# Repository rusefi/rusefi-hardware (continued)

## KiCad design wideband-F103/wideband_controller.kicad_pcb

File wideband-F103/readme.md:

🔴 RED ALERT 🔴 STATUS UNKNOWN 🔴 Most usages are either F042 or lambda-x2, this wideband-F103 design is a bit abandoned we never got perfect HW+FW match 🔴

Self-contained LSU wideband supporting both STM32F103 and GD32F103

See https://github.com/mck1117/wideband

115200 baud

[.ini](https://github.com/dron0gus/wideband/blob/master/firmware/ini/rusefi_wb_f1.ini)

# Changelog

# rev 4

* Iteration of rev 3 with fixed PCB dimensions
* Improved RC filter on digital input lines
* Pinout changes https://github.com/rusefi/rusefi-hardware/pull/153

# rev 3

* New board
* Microcontroller replaced
* Added four digital inputs
* Added bluetooth module
* Now LQFP-64
* In-action demo https://youtu.be/ZzZXdSdfkbs

# rev 2

* Firmware binaries https://github.com/rusefi/rusefi-hardware/releases/tag/20220904
* Silkscreen improvements on back side
* 2x7 debug port moved to top side
* VBatt sense added
* Still LQFP-48

# rev 1

* Works with LQFP-48 STM32 and GD32
* PWM required HW hacks

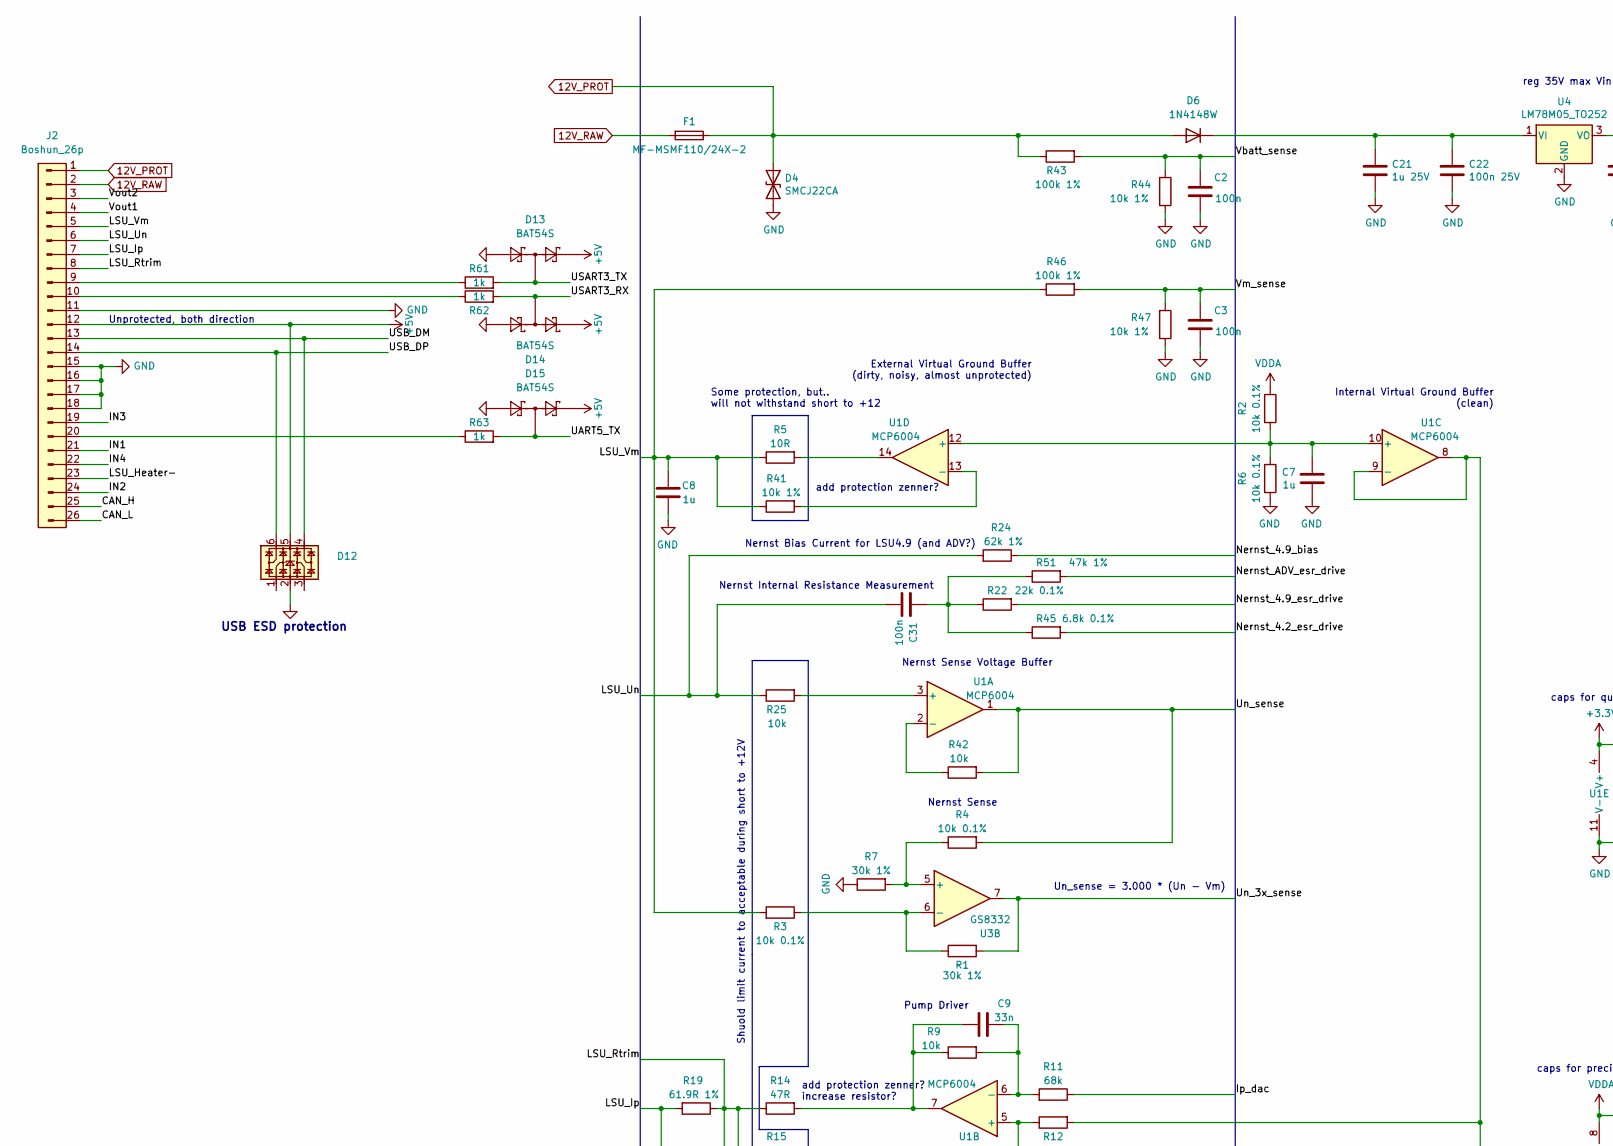
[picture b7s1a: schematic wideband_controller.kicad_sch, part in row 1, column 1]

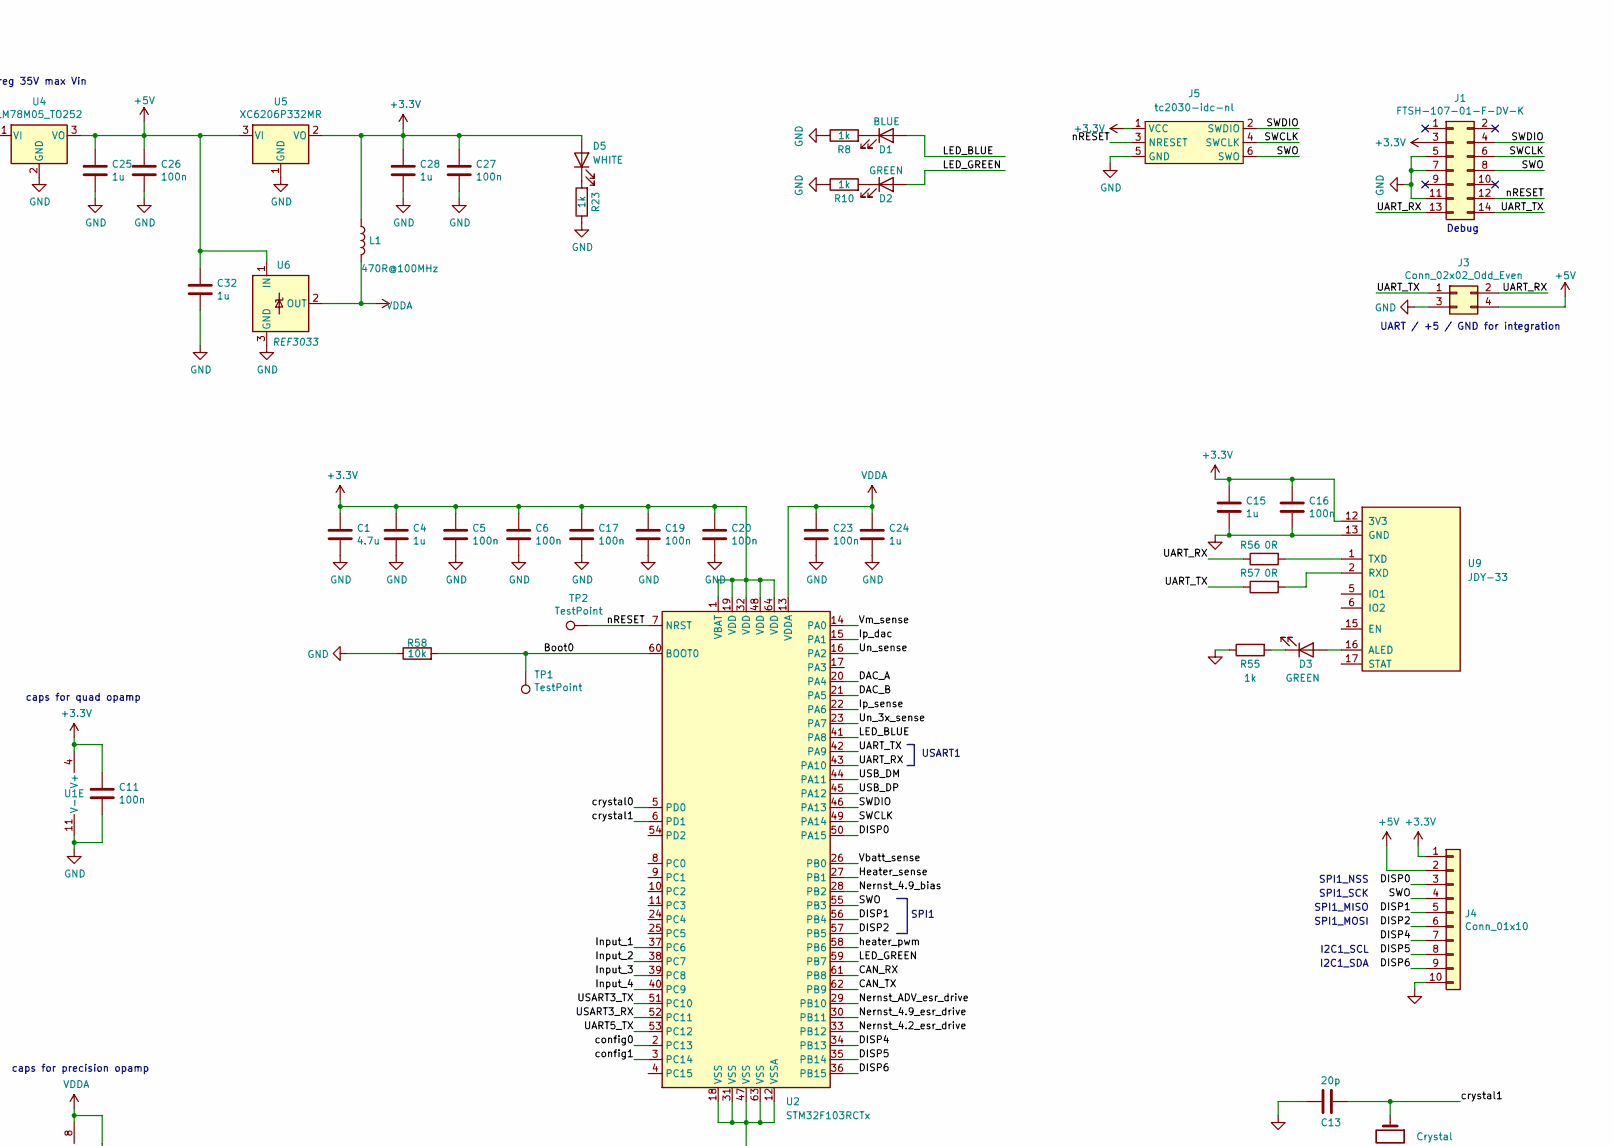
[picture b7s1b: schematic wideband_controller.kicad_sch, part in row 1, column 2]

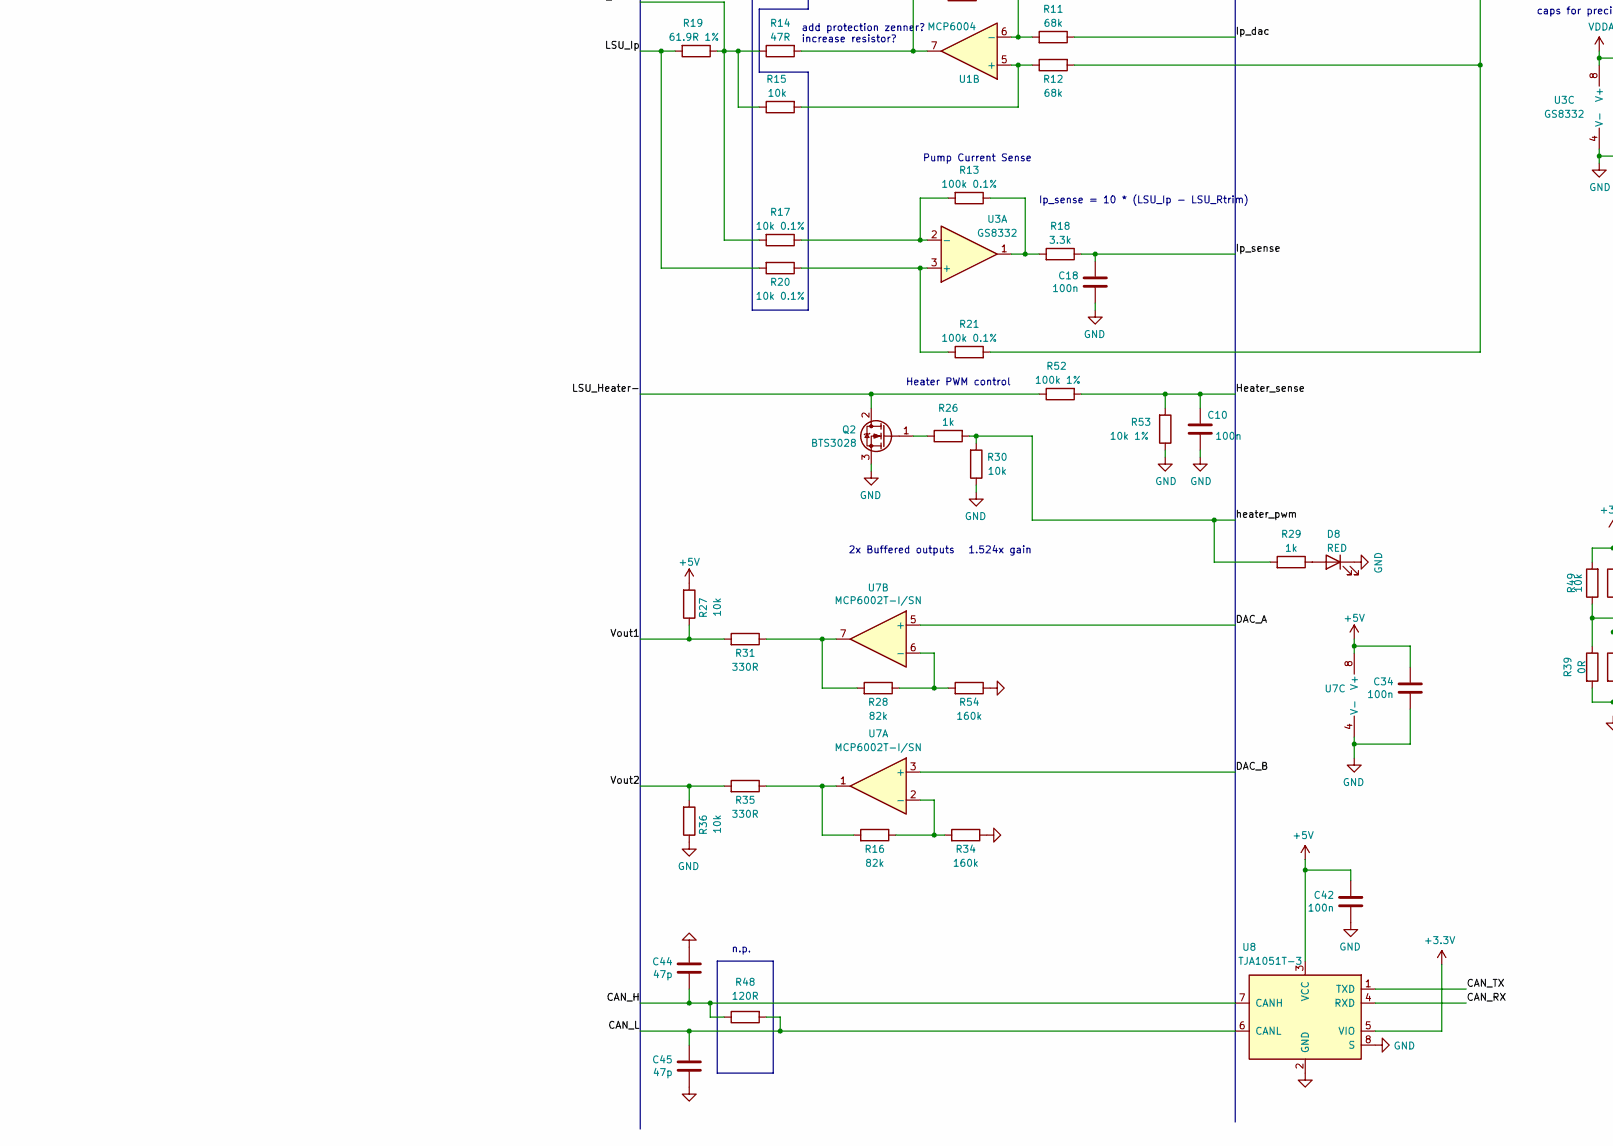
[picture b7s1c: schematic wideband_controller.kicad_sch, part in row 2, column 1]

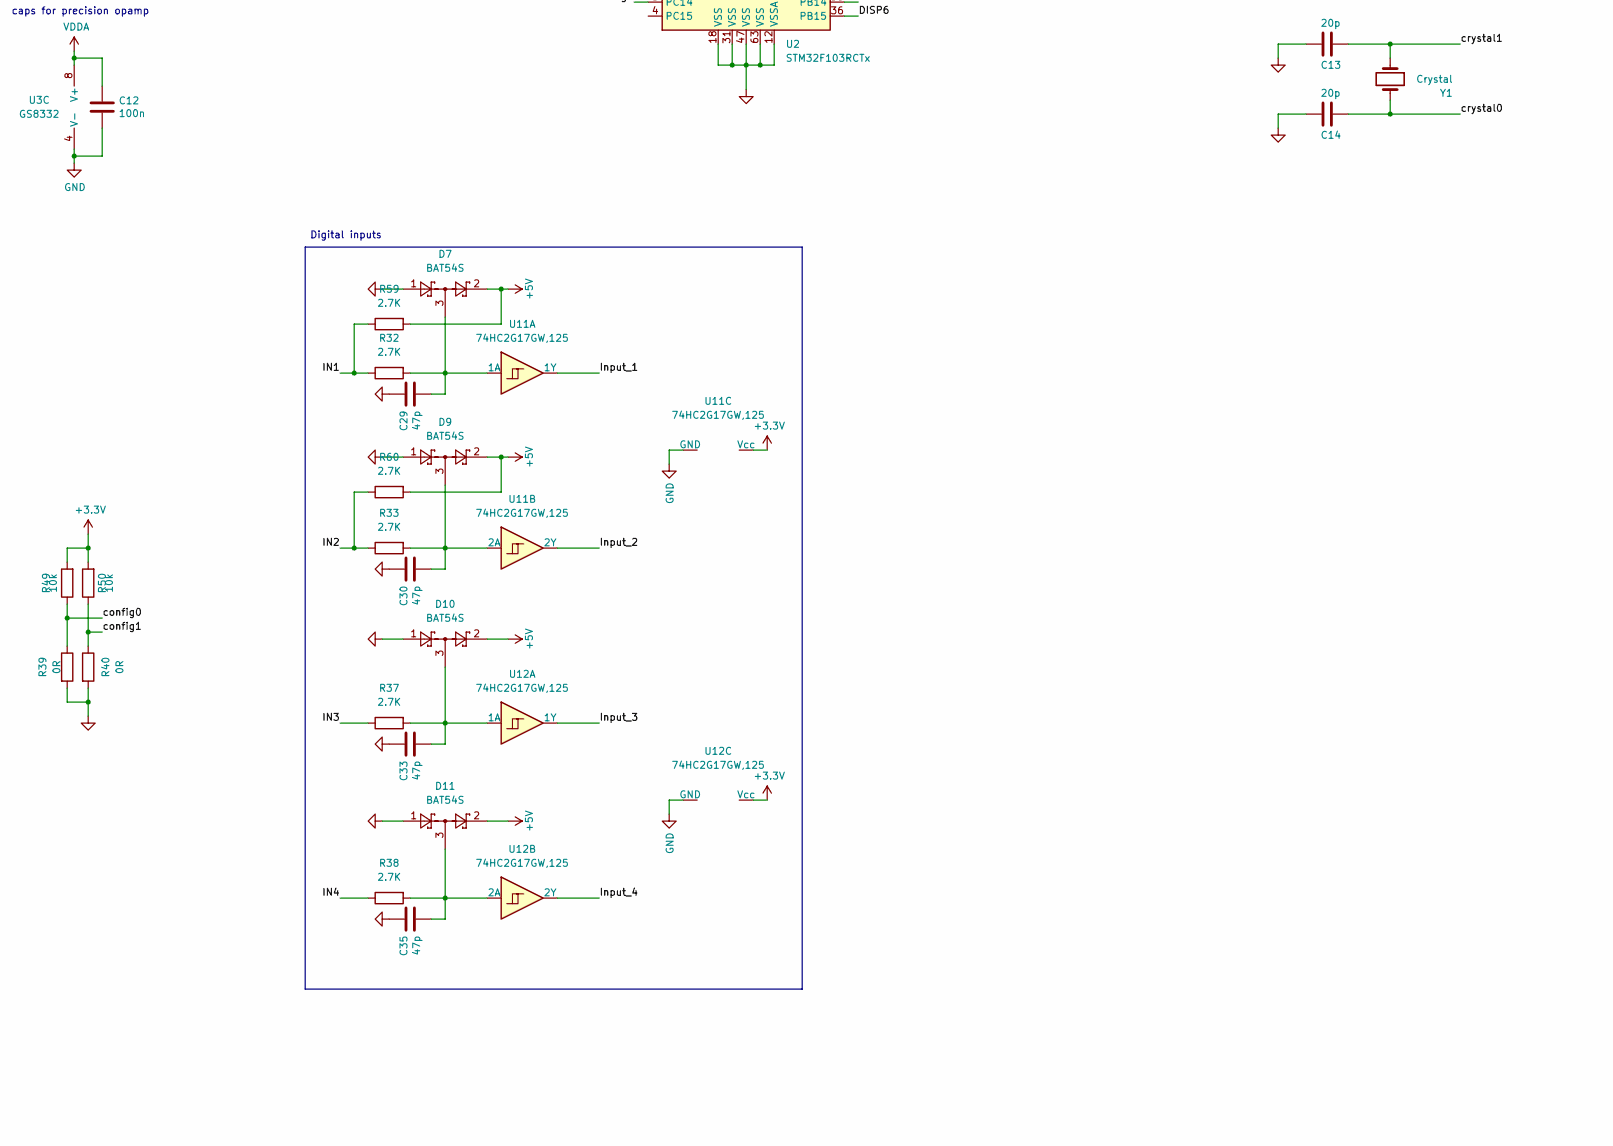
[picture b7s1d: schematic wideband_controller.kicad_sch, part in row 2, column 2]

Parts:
C1: 4.7u; C_0402_1005Metric; LCSC C23733
C2, C3, C5, C6, C10, C11, C12, C16, C17, C18, C19, C20, C23, C26, C27, C31, C34, C42: 100n; C_0402_1005Metric; LCSC C1525
C4, C7, C8, C15, C24, C25, C28, C32: 1u; C_0402_1005Metric; LCSC C52923
C9: 33n; C_0402_1005Metric; LCSC C1585
C13, C14: 20p; C_0402_1005Metric; LCSC C52923
C21: 1u 25V; C_0603_1608Metric; LCSC C15849
C22: 100n 25V; C_0603_1608Metric; LCSC C14663
C29, C30, C33, C35, C44, C45: 47p; C_0402_1005Metric; LCSC C1567
D1: BLUE; LED_0603_1608Metric; LCSC C72041
D2, D3: GREEN; LED_0603_1608Metric; LCSC C72043
D4: SMCJ22CA; D_SMC; LCSC C310038
D5: WHITE; LED_0603_1608Metric; LCSC C2290
D6: 1N4148W; D_SOD-123; LCSC C81598
D7, D9, D10, D11, D13, D14, D15: BAT54S; SOT-23; LCSC C2903789
D8: RED; LED_0603_1608Metric; LCSC C2286
D12: TSOP-6; LCSC C85364
F1: MF-MSMF110/24X-2; Fuse_1812_4532Metric_Pad1.30x3.40mm_HandSolder; JLCPCB C210835
J1: FTSH-107-01-F-DV-K; PinHeader_2x07_P1.27mm_Vertical_SMD
J2: Boshun_26p; Boshun_26pin
J3: Conn_02x02_Odd_Even; PinHeader_2x02_P2.54mm_Vertical
J4: Conn_01x10; PinHeader_1x10_P2.54mm_Vertical
J5: tc2030-idc-nl
L1: 470R@100MHz; L_0603_1608Metric; LCSC C97853
Q2: BTS3028; TO-252-2; LCSC C112639
R1, R7: 30k 1%; R_0603_1608Metric; LCSC C22984
R2, R3, R4, R6, R17, R20: 10k 0.1%; R_0603_1608Metric; LCSC C309083
R5: 10R; R_1206_3216Metric; LCSC C17903
R8, R10, R23, R26, R29, R55, R61, R62, R63: 1k; R_0402_1005Metric; LCSC C11702
R9, R15, R25, R27, R36, R42, R49, R50, R58: 10k; R_0402_1005Metric; LCSC C25744
R11, R12: 68k; R_0402_1005Metric; LCSC C36871
R13, R21: 100k 0.1%; R_0603_1608Metric; LCSC C122538
R14: 47R; R_0603_1608Metric; LCSC C328363
R16, R28: 82k; R_0603_1608Metric; LCSC C23254
R18: 3.3k; R_0402_1005Metric; LCSC C25890
R19: 61.9R 1%; R_0805_2012Metric; LCSC C322537
R22: 22k 0.1%; R_0603_1608Metric; LCSC C133163
R24: 62k 1%; R_0603_1608Metric; LCSC C23221
R30: 10k; R_0402_1005Metric; LCSC C11702
R31, R35: 330R; R_0603_1608Metric; LCSC C23138
R32, R33, R37, R38, R59, R60: 2.7K; R_1206_3216Metric; JLCPCB C17950
R34, R54: 160k; R_0603_1608Metric; LCSC C22813
R39, R40: 0R; R_0402_1005Metric; LCSC C325377
R41, R44, R47, R53: 10k 1%; R_0402_1005Metric; LCSC C25744
R43, R46, R52: 100k 1%; R_0402_1005Metric; LCSC C25741
R45: 6.8k 0.1%; R_0603_1608Metric; LCSC C705876
R48: 120R; R_1206_3216Metric; LCSC C176250
R51: 47k 1%; R_0603_1608Metric; LCSC C25819
R56, R57: 0R; R_0402_1005Metric; JLCPCB C17168
TP1, TP2: TestPoint; PinHeader_1x01_P2.54mm_Vertical
U1: MCP6004; TSSOP-14_4.4x5mm_P0.65mm; LCSC C50282
U2: STM32F103RCTx; LQFP-64_10x10mm_P0.5mm
U3: GS8332; TSSOP-8_3x3mm_P0.65mm; LCSC C157714
U4: LM78M05_TO252; TO-252-2; LCSC C58069
U5: XC6206P332MR; SOT-23; LCSC C5446
U6: REF3033; SOT-23; LCSC C36658
U7: MCP6002T-I/SN; SO-8_3.9x4.9mm_P1.27mm; LCSC C7377
U8: TJA1051T-3; SOIC-8_3.9x4.9mm_P1.27mm; LCSC C38695
U9: JDY-33; PARTREV v1.0
U11, U12: 74HC2G17GW,125; SOT-23-6; LCSC C94189
Y1: Crystal; Crystal_SMD_HC49-SD; JLCPCB C108703

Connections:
12V_PROT: D4.1 (A1), D6.2 (A), F1.1, J2.1, R43.1
12V_RAW: F1.2, J2.2
+3V3: C1.1, C4.1, C5.1, C6.1, C11.1, C15.1, C16.1, C17.1, C19.1, C20.1, C27.1, C28.1, D5.2 (A), J1.3, J4.1, J5.1 (VCC), L1.1, R49.2, R50.2, U1.4 (V+), U2.1 (VBAT), U2.19 (VDD), U2.32 (VDD), U2.48 (VDD), U2.64 (VDD), U5.2 (VO), U8.5 (VIO), U9.12 (3V3), U11.5 (Vcc), U12.5 (Vcc)
+5V: C25.1, C26.1, C32.1, C34.1, C42.1, D7.2, D9.2, D10.2, D11.2, D12.5, D13.2, D14.2, D15.2, J2.12, J3.4, J4.2, R27.2, R59.2, R60.2, U4.3 (VO), U5.3 (VI), U6.1 (IN), U7.8 (V+), U8.3 (VCC)
/Boot0: R58.2, TP1.1, U2.60 (BOOT0)
/CAN_H: C44.2, J2.25, R48.1, U8.7 (CANH)
/CAN_L: C45.1, J2.26, R48.2, U8.6 (CANL)
/CAN_RX: U2.61 (PB8), U8.4 (RXD)
/CAN_TX: U2.62 (PB9), U8.1 (TXD)
/DAC_A: U2.20 (PA4), U7.5 (+)
/DAC_B: U2.21 (PA5), U7.3 (+)
/DISP0: J4.3, U2.50 (PA15)
/DISP1: J4.5, U2.56 (PB4)
/DISP2: J4.6, U2.57 (PB5)
/DISP4: J4.7, U2.34 (PB13)
/DISP5: J4.8, U2.35 (PB14)
/DISP6: J4.9, U2.36 (PB15)
/Heater_sense: C10.1, R52.2, R53.2, U2.27 (PB1)
/IN1: J2.21, R32.1, R59.1
/IN2: J2.24, R33.1, R60.1
/IN3: J2.19, R37.1
/IN4: J2.22, R38.1
/Input_1: U2.37 (PC6), U11.6 (1Y)
/Input_2: U2.38 (PC7), U11.4 (2Y)
/Input_3: U2.39 (PC8), U12.6 (1Y)
/Input_4: U2.40 (PC9), U12.4 (2Y)
/Ip_dac: R11.1, U2.15 (PA1)
/Ip_sense: C18.1, R18.1, U2.22 (PA6)
/LED_BLUE: D1.2 (A), U2.41 (PA8)
/LED_GREEN: D2.2 (A), U2.59 (PB7)
/LSU_Heater-: J2.23, Q2.2 (D), R52.1
/LSU_Ip: J2.7, R19.2, R20.2
/LSU_Rtrim: J2.8, R14.1, R15.1, R17.2, R19.1
/LSU_Un: C31.1, J2.6, R24.2, R25.1
/LSU_Vm: C8.1, J2.5, R3.2, R5.1, R41.1, R46.1
/Nernst_4.2_esr_drive: R45.2, U2.33 (PB12)
/Nernst_4.9_bias: R24.1, U2.28 (PB2)
/Nernst_4.9_esr_drive: R22.2, U2.30 (PB11)
/Nernst_ADV_esr_drive: R51.2, U2.29 (PB10)
/SWCLK: J1.6, J5.4 (SWCLK), U2.49 (PA14)
/SWDIO: J1.4, J5.2 (SWDIO), U2.46 (PA13)
/SWO: J1.8, J4.4, J5.6 (SWO), U2.55 (PB3)
/UART5_TX: D15.3, R63.2, U2.53 (PC12)
/UART_RX: J1.13, J3.2, R56.1, U2.43 (PA10)
/UART_TX: J1.14, J3.1, R57.1, U2.42 (PA9)
/USART3_RX: D14.3, R62.2, U2.52 (PC11)
/USART3_TX: D13.3, R61.2, U2.51 (PC10)
/USB_DM: D12.4, J2.13, U2.44 (PA11)
/USB_DP: D12.6, J2.14, U2.45 (PA12)
/Un_3x_sense: R1.2, U2.23 (PA7), U3.7
/Un_sense: R4.2, R42.2, U1.1, U2.16 (PA2)
/Vbatt_sense: C2.1, R43.2, R44.2, U2.26 (PB0)
/Vm_sense: C3.1, R46.2, R47.2, U2.14 (PA0)
/Vout1: J2.4, R27.1, R31.2
/Vout2: J2.3, R35.2, R36.2
/config0: R39.1, R49.1, U2.2 (PC13)
/config1: R40.1, R50.1, U2.3 (PC14)
/crystal0: C14.1, U2.5 (PD0), Y1.2
/crystal1: C13.1, U2.6 (PD1), Y1.1
/heater_pwm: R26.2, R29.2, R30.2, U2.58 (PB6)
/nRESET: J1.12, J5.3 (NRESET), TP2.1, U2.7 (NRST)
GND: C1.2, C2.2, C3.2, C4.2, C5.2, C6.2, C7.2, C8.2, C10.2, C11.2, C12.2, C13.2, C14.2, C15.2, C16.2, C17.2, C18.2, C19.2, C20.2, C21.2, C22.2, C23.2, C24.2, C25.2, C26.2, C27.2, C28.2, C29.1, C30.1, C32.2, C33.1, C34.2, C35.1, C42.2, C44.1, C45.2, D4.2 (A2), D7.1, D8.1 (K), D9.1, D10.1, D11.1, D12.2, D13.1, D14.1, D15.1, J1.5, J1.7, J1.11, J2.11, J2.15, J2.16, J2.17, J2.18, J3.3, J4.10, J5.5 (GND), Q2.3 (S), R6.2, R7.1, R8.1, R10.1, R23.1, R30.1, R34.1, R36.1, R39.2, R40.2, R44.1, R47.1, R53.1, R54.1, R55.1, R58.1, U1.11 (V-), U2.12 (VSSA), U2.18 (VSS), U2.31 (VSS), U2.47 (VSS), U2.63 (VSS), U3.4 (V-), U4.2 (GND), U5.1 (GND), U6.3 (GND), U7.4 (V-), U8.2 (GND), U8.8 (S), U9.13 (GND), U11.2 (GND), U12.2 (GND)
unnamed: C7.1, R2.2, R6.1, U1.10 (+), U1.12 (+)
unnamed: C9.1, R9.1, R14.2, U1.7
unnamed: C9.2, R9.2, R11.2, U1.6 (-)
unnamed: C21.1, C22.1, D6.1 (K), U4.1 (VI)
unnamed: C29.2, D7.3, R32.2, U11.1 (1A)
unnamed: C30.2, D9.3, R33.2, U11.3 (2A)
unnamed: C31.2, R22.1, R45.1, R51.1
unnamed: C33.2, D10.3, R37.2, U12.1 (1A)
unnamed: C35.2, D11.3, R38.2, U12.3 (2A)
unnamed: D1.1 (K), R8.2
unnamed: D2.1 (K), R10.2
unnamed: D3.1 (K), R55.2
unnamed: D3.2 (A), U9.16 (ALED)
unnamed: D5.1 (K), R23.2
unnamed: D8.2 (A), R29.1
unnamed: J2.9, R61.1
unnamed: J2.10, R62.1
unnamed: J2.20, R63.1
unnamed: Q2.1 (G), R26.1
unnamed: R1.1, R3.1, U3.6 (-)
unnamed: R4.1, R7.2, U3.5 (+)
unnamed: R5.2, U1.14
unnamed: R12.1, R15.2, U1.5 (+)
unnamed: R12.2, R21.2, U1.8, U1.9 (-)
unnamed: R13.1, R18.2, U3.1
unnamed: R13.2, R17.1, U3.2 (-)
unnamed: R16.1, R34.2, U7.2 (-)
unnamed: R16.2, R35.1, U7.1
unnamed: R20.1, R21.1, U3.3 (+)
unnamed: R25.2, U1.3 (+)
unnamed: R28.1, R54.2, U7.6 (-)
unnamed: R28.2, R31.1, U7.7
unnamed: R41.2, U1.13 (-)
unnamed: R42.1, U1.2 (-)
unnamed: R56.2, U9.1 (TXD)
unnamed: R57.2, U9.2 (RXD)
VDDA: C12.1, C23.1, C24.1, L1.2, R2.1, U2.13 (VDDA), U3.8 (V+), U6.2 (OUT)

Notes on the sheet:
Nernst Internal Resistance Measurement
Pump Current Sense
Ip_sense = 10 * (LSU_Ip - LSU_Rtrim)
reg 35V max Vin
SPI1_MOSI
Unprotected, both direction
Shuold limit current to acceptable during short to +12V
Internal Virtual Ground Buffer (clean)
I2C1_SCL
External Virtual Ground Buffer (dirty, noisy, almost unprotected)
Pump Driver
USB ESD protection
Nernst Sense
Un_sense = 3.000 * (Un - Vm)
Nernst Bias Current for LSU4.9 (and ADV?)
Digital inputs
Debug
n.p.
add protection zenner? increase resistor?
2x Buffered outputs
caps for precision opamp
Some protection, but.. will not withstand short to +12
SPI1
1.524x gain
SPI1_SCK
Nernst Sense Voltage Buffer
add protection zenner?
SPI1_NSS
caps for quad opamp
Heater PWM control
USART1
I2C1_SDA
UART / +5 / GND for integration
SPI1_MISO

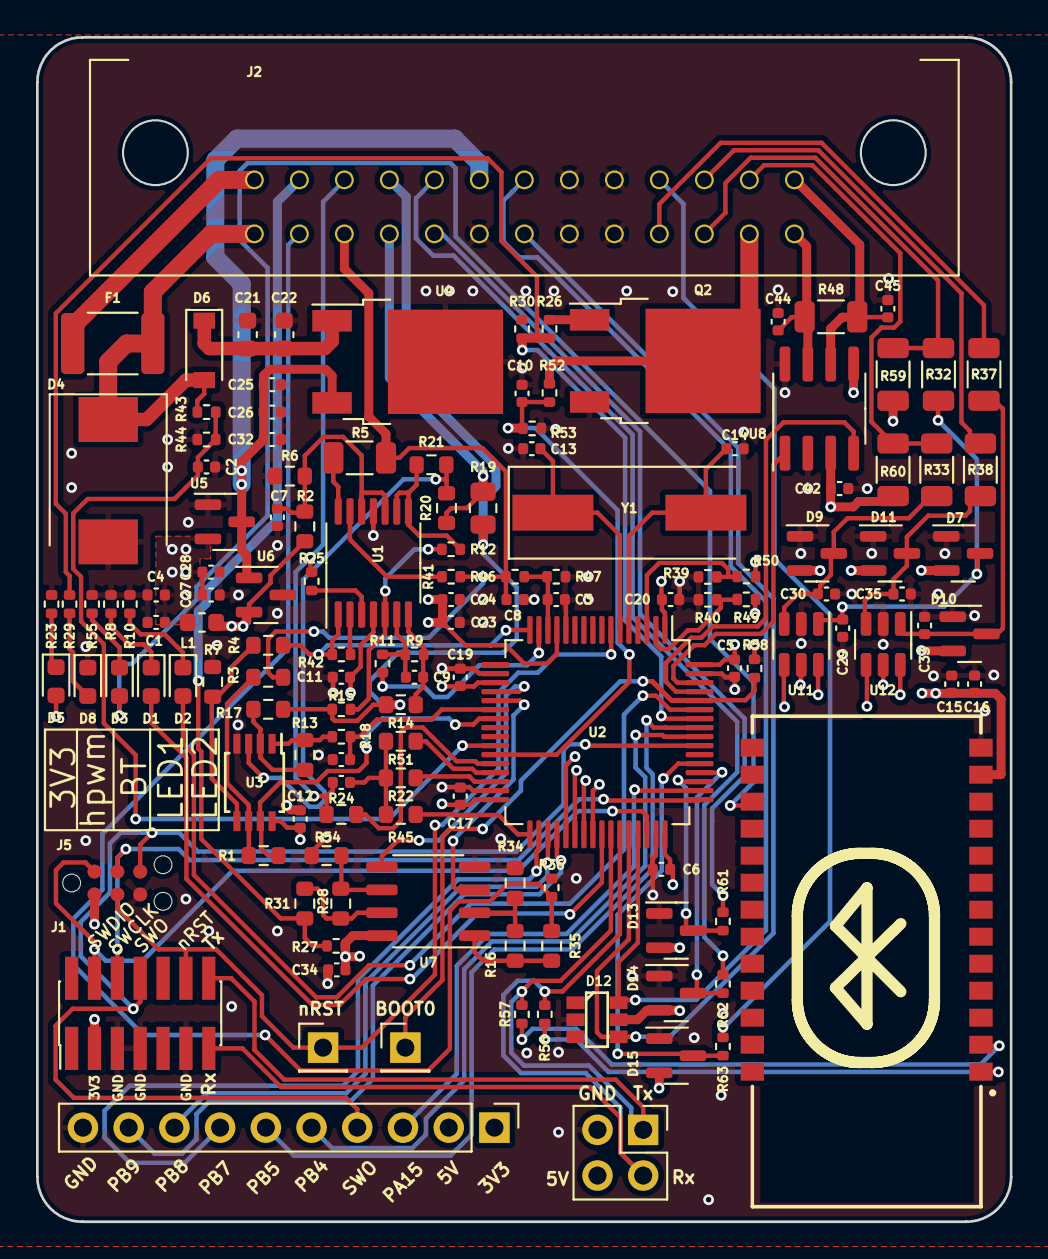
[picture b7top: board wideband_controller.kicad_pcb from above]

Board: 4 copper layers, 54.1 x 65.8 mm, 138 parts (0 on the bottom side), 99 nets.

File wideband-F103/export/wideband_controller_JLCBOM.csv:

Comment,Designator,Footprint,LCSC
"1u","C1,C6,C7,C8,C25,C28,C32","Capacitor_SMD:C_0402_1005Metric","C52923"
"100n","C2,C3,C5,C10,C11,C12,C18,C26,C27,C31,C34,C38,C39,C40,C41,C42","Capacitor_SMD:C_0402_1005Metric","C1525"
"1u  25V","C21","Capacitor_SMD:C_0603_1608Metric","C15849"
"100n  25V","C22","Capacitor_SMD:C_0603_1608Metric","C14663"
"2.2u","C33,C36","Capacitor_SMD:C_0402_1005Metric","C12530"
"4.7u","C4","Capacitor_SMD:C_0402_1005Metric","C23733"
"47p","C44,C45","Capacitor_SMD:C_0402_1005Metric","C1567"
"33n","C9","Capacitor_SMD:C_0402_1005Metric","C1585"
"BLUE","D1","LED_SMD:LED_0603_1608Metric","C72041"
"GREEN","D2","LED_SMD:LED_0603_1608Metric","C72043"
"SMCJ22CA","D4","Diode_SMD:D_SMC","C310038"
"WHITE","D5","LED_SMD:LED_0603_1608Metric","C2290"
"1N4148W","D6","Diode_SMD:D_SOD-123","C2128"
"RED","D8","LED_SMD:LED_0603_1608Metric","C2286"
"Fuse","F1","Fuse:Fuseholder_Blade_Mini_Keystone_3568",""
"FTSH-107-01-F-DV-K","J1","Connector_PinHeader_1.27mm:PinHeader_2x07_P1.27mm_Vertical_SMD",""
"Conn_02x06_Top_Bottom","J2","db_footprints:MX120G_12",""
"Conn_02x02_Odd_Even","J3","Connector_PinHeader_2.54mm:PinHeader_2x02_P2.54mm_Vertical",""
"Conn_01x10","J4","Connector_PinHeader_2.54mm:PinHeader_1x10_P2.54mm_Vertical",""
"BTS3028","Q2","Package_TO_SOT_SMD:TO-252-2","C112639"
"30k 1%","R1,R7","Resistor_SMD:R_0603_1608Metric","C25776"
"68k","R11,R12","Resistor_SMD:R_0402_1005Metric","C36871"
"100k 0.1%","R13,R21","Resistor_SMD:R_0603_1608Metric","C54345"
"47R","R14","Resistor_SMD:R_0603_1608Metric","C328363"
"3.3k","R18,R28,R34","Resistor_SMD:R_0402_1005Metric","C25890"
"61.9R 1%","R19","Resistor_SMD:R_0603_1608Metric","C23092"
"10k 0.1%","R2,R3,R4,R6,R17,R20","Resistor_SMD:R_0603_1608Metric","C39050"
"22k 0.1%","R22","Resistor_SMD:R_0603_1608Metric","C133163"
"62k 1%","R24","Resistor_SMD:R_0603_1608Metric","C23221"
"330R","R31,R35","Resistor_SMD:R_0603_1608Metric","C23138"
"82k","R32,R37","Resistor_SMD:R_0603_1608Metric","C23254"
"160k","R33,R38","Resistor_SMD:R_0603_1608Metric","C22813"
"0R","R39,R40","Resistor_SMD:R_0402_1005Metric","C325377"
"10k 1%","R41,R44,R47,R53","Resistor_SMD:R_0402_1005Metric","C25744"
"100k 1%","R43,R46,R52","Resistor_SMD:R_0402_1005Metric","C25741"
"6.8k 0.1%","R45","Resistor_SMD:R_0603_1608Metric","C705876"
"10R","R5","Resistor_SMD:R_1206_3216Metric","C17903"
"47k 1%","R51","Resistor_SMD:R_0603_1608Metric","C25819"
"1k","R8,R10,R23,R26,R29","Resistor_SMD:R_0402_1005Metric","C11702"
"10k","R9,R15,R16,R25,R27,R30,R36,R42,R49,R50","Resistor_SMD:R_0402_1005Metric","C25744"
"TestPoint","TP1,TP2","Connector_PinHeader_2.54mm:PinHeader_1x01_P2.54mm_Vertical",""
"TestPoint","TP3,TP4,TP5","TestPoint:TestPoint_Pad_D1.0mm",""
"MCP6004","U1","Package_SO:TSSOP-14_4.4x5mm_P0.65mm","C50282"
"STM32F103C6Tx","U2","Package_QFP:LQFP-48_7x7mm_P0.5mm",""
"GS8332","U3","Package_SO:TSSOP-8_3x3mm_P0.65mm","C157714"
"LM78M05_TO252","U4","Package_TO_SOT_SMD:TO-252-2","C58069"
"XC6206P332MR","U5","Package_TO_SOT_SMD:SOT-23","C5446"
"REF3033","U6","Package_TO_SOT_SMD:SOT-23","C36658"
"MCP6002T-I/SN","U7","Package_SO:SO-8_3.9x4.9mm_P1.27mm","C7377"
"TJA1051T-3","U8","Package_SO:SOIC-8_3.9x4.9mm_P1.27mm","C38695"
